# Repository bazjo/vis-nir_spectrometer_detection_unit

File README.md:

# vis-nir_spectrometer_detection_unit
This project contains a high-resolution detection unit for VIS/NIR spectroscopy using the Hamamatsu S1337-1010 photodiode and the Analog AD7768-1 24 Bit ADC.

It was developed as a student project in the summer term of 2020 in the course "Optical Spectroscopy and its Applications" at Cologne University of Applied Sciences.

## Getting Started

The PCB is designed to utilize an Arduino shield footprint for use with various breakout boards, such as ST Nucleo STM32 development boards or the avnet MiniZed development platform for Xilinx Zynq.

It features power filtering and an -5V inverter, the AD7768-1 DC to 204 kHz 24-Bit ADC (connected via SPI) with a 4.096 V ADR4540 and a photodiode front end featuring the AD8622 OpAmp. When a tunable clock is not available, i.e. when no FPGA is used, the main clock can be provided by an Si514 Any Frequency Programmable Oscillator (connected via I2C).

The photodiode is attached at the front to be mounted inside the spectrometer.

When assembling the PCB please look out for the bodges/errata. The PCB has been designed using kicad.

Demo applications are provided for the Arduino platform (just for the Si514 as the AD7768-1 requires 16-Bit SPI which is not yet supported by Arduino) and the STM32 platform. This application is designed for the Nucleo F401RE and was developed using the Crossley CrossWorks for ARM IDE. The code can be compiled with the trial version. This demo Application continuously sends data to a connected computer at 300 Sp/s via a serial connection.

## Theory of Operation

### Pinout
[jumpered] Pins must be connected by a designated jumper resistor.

Arduino Pin | STM32F401RE Pin | Connection
---|---|---
D0|PA3|none (!DRDY if not bodged)
D1|PA2|[jumpered] AD7768-1 !RESET
D2|PA10|[jumpered] AD7768-1 GPIO0
D3|PB3|[jumpered] AD7768-1 GPIO1
D4|PB5|[jumpered] AD7768-1 GPIO2
D5|PB4|[jumpered] AD7768-1 GPIO3
D6|PB10|[jumpered] AD7768-1 MCLK
D7|PA8|AD7768-1 !DRDY after bodge
D10|PB6|AD7768-1 !CS
D11|PA7|AD7768-1 MOSI
D12|PA6|AD7768-1 MISO
D13|PA5|AD7768-1 SCK
SDA|PB9|Si514 SDA
SCL|PB8|Si514 SCL

### Bodges/Errata
There are two problems with the pcb which are minor enough not to roll out a new revision
1. The Arduino RX/TX pins are used for GPIO. Unfortunately those Pins are used for the VCP connection on the Nucleo boards as well. The needed connection !DRDY is therefore rerouted to pin D7. This bodge can be performed by drilling the via on !DRDY with 0.8 mm drill bit and soldering a bodge wire between TP6 and D7.
2. When using the ADC on it's own, sync pulses can be generated via SPI. Those need to be send from SYNC_OUT to SYNC_IN. For this, bridge TP4 and TP5 with a 1206 0R resistor.

### PSU
The circuit uses three voltage rails. The 3V3 and 5V rails are used straight from the baseboard and are filtered through a 2-Stage LC PI-filter. The -5V rail is generated locally with TPS63700 inverter and subsequent LM2991 LDO. Power Planes are located on the second inner layer of the PCB. there are different planes for analog and digital ground, whose domains are joint below the high-speed adc interface to prevent loop currents.

### Oscillator
The Si514 Oscillator is attached via I2C and is equipped with pullup resistors. The source for the ADC MCLK can be selected between Si514 and baseboard via means of the resistor jumpers R24/R29. The tap R29 could also be used for MCLK monitoring.

### ADC + Frontend
The AD7768 was chosen for a few different reasons. First of all, it is a 24-Bit ADC suitable for low frequencies and even DC. Further, it features digital signal processing capabilities difficult to implement in a MCU. Most importantly, it allows for a wide range of decimation rates and a highly customizable sample rate so that acquisitions can be matched to the speed of a wavelength selective element. The ADC is connected via SPI. It is used in a pseudo-differential configuration with a 4.096 V reference ADR4540, to measure a voltage range between 0 an 4.096 V. The lowest possible sample rate with the highest decimation of 1024x is 300 Sp/s.

The ADC is paired with a transimpedance photodiode amplifier which is realized upon 1/2 of an AD8622 OpAmp. The values of the feedback network are matched in accordance to the photodiode sensitivity and speed. The photodiodes anode can be connected to ground via R23 or the diode can be reversed biased via R22. Reverse bias is generated through the other 1/2 of the AD8622 buffering an voltage divider R25/R26.

The photodiode is a Hamamatsu S1337-1010. It's spectral response from 190/340-1100 nm enables its use in VIS and certain NIR applications. The large area guarantees a high photosensitivity, and the rise time is fast enough for the desired spectroscopy application.

## Software Examples
The included software provides functions to interface with the hardware on the PCB.

The function `Set_Si514_Frequency()` configures the Si514 and has to be executed after every restart. It expects an array of register values which can be calculated through the Silab Utility provided in /resources/tools.

The functions to read an write from/to the AD7768-1 registers in general feature 8 bit wide addresses and values. An exemption is the result register, which is 24 bit wide an therefore is internally handled as an uint32.

After the ICs are configured, a SYNC pulse is triggered which starts the continuous adc capture. Every time a new sample is ready, a falling edge is presented to the MCU by the adc on !DRDY which is captured through an interrupt, and sets a flag, which enables a readout in the main program loop. Depending upon configuration of the variable `average_mode`, the result is either output through a serial connection right away, or after 256 samples have been averaged.

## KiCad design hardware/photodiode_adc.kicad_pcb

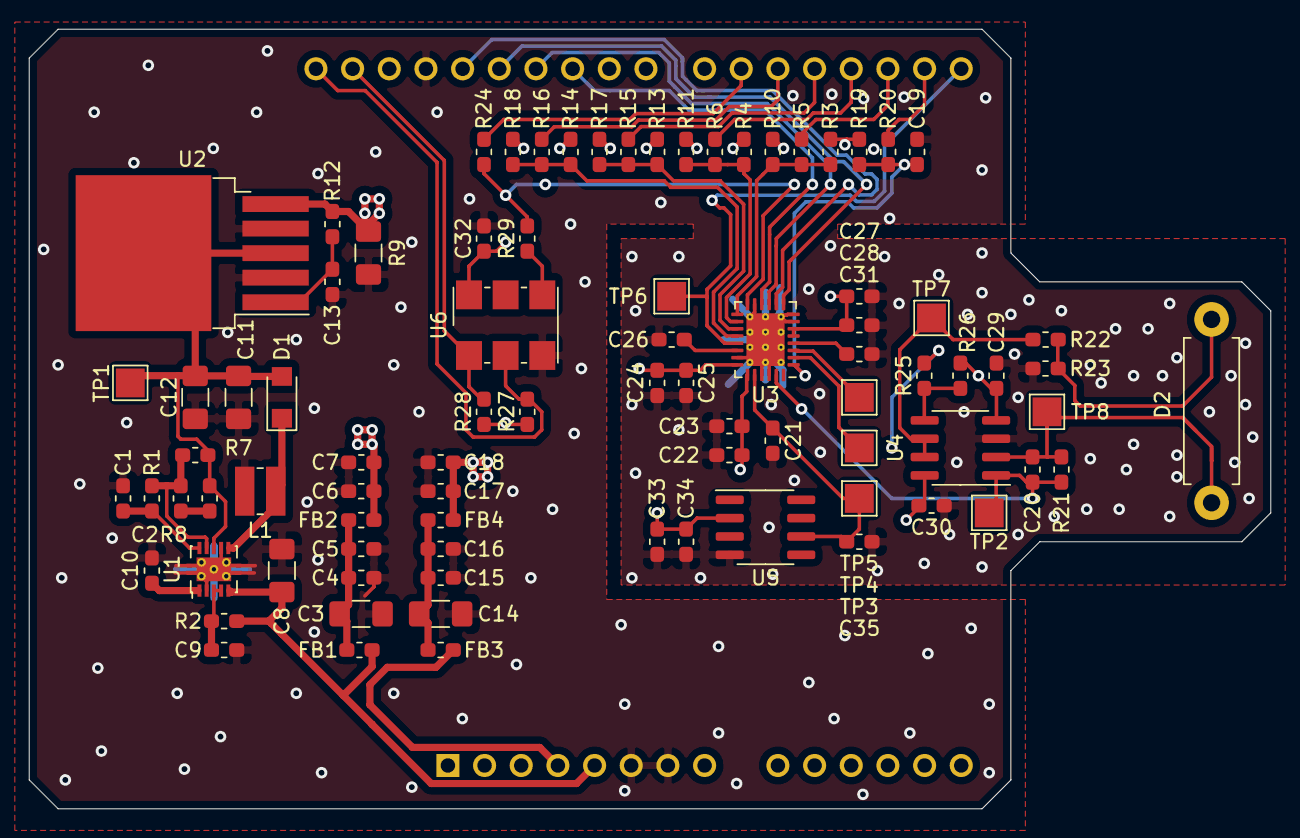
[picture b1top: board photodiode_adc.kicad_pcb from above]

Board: 4 copper layers, 86.0 x 54.0 mm, 86 parts (1 on the bottom side), 45 nets.

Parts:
A1: Arduino_UNO_R3; Arduino_UNO_R3_NoSilk
C1: 220n; C_0603_1608Metric_Pad1.05x0.95mm_HandSolder
C2: 10p; C_0603_1608Metric_Pad1.05x0.95mm_HandSolder
C3, C8, C12, C13, C14: 10u; C_1206_3216Metric_Pad1.42x1.75mm_HandSolder
C4, C6, C15, C17, C22, C24, C26, C27, C31, C33: 1u; C_0603_1608Metric_Pad1.05x0.95mm_HandSolder
C5, C7, C9, C16, C18, C19, C21, C23, C25, C28, C29, C30, C32, C34, C35: 100n; C_0603_1608Metric_Pad1.05x0.95mm_HandSolder
C10: 4n7; C_0603_1608Metric_Pad1.05x0.95mm_HandSolder
C11: 22u; C_1206_3216Metric_Pad1.42x1.75mm_HandSolder
C20: 360p; C_0603_1608Metric_Pad1.05x0.95mm_HandSolder
D1: D_Schottky; D_SMF
D2: D_Photo_ALT; R_Axial_DIN0411_L9.9mm_D3.6mm_P12.70mm_Horizontal
FB1, FB2, FB3, FB4: Ferrite_Bead_Small; C_0603_1608Metric_Pad1.05x0.95mm_HandSolder
L1: 4u7; L_Wuerth_MAPI-3020
R1: 150k; R_0603_1608Metric_Pad1.05x0.95mm_HandSolder
R2: 10R; R_0603_1608Metric_Pad1.05x0.95mm_HandSolder
R3, R4, R5, R6, R10, R11, R13, R14, R15, R16, R17, R18, R19, R20, R22, R23, R24, R29: 0R; R_0603_1608Metric_Pad1.05x0.95mm_HandSolder
R7: 742k; R_0603_1608Metric_Pad1.05x0.95mm_HandSolder
R8, R12: 100k; R_0603_1608Metric_Pad1.05x0.95mm_HandSolder
R9: 32k; R_0603_1608Metric_Pad1.05x0.95mm_HandSolder
R21: 42.2k; R_0603_1608Metric_Pad1.05x0.95mm_HandSolder
R25, R26: R; R_0603_1608Metric_Pad1.05x0.95mm_HandSolder
R27, R28: 4k7; R_0603_1608Metric_Pad1.05x0.95mm_HandSolder
TP1, TP2, TP3, TP4, TP5, TP6, TP7, TP8: TestPoint; TestPoint_Pad_2.0x2.0mm
U1: TPS63700; VSON-10-1EP_3x3mm_P0.5mm_EP1.65x2.4mm_ThermalVias
U2: LM2991; TO-263-5_TabPin6
U3: AD7768-1; QFN-28-1EP_4x5mm_P0.5mm_EP2.65x3.65mm_ThermalVias
U4: AD8622; SOIC-8_3.9x4.9mm_P1.27mm
U5: ADR452x; SOIC-8_3.9x4.9mm_P1.27mm
U6: Si514; Oscillator_SMD_IDT_JU6-6_7.0x5.0mm_P2.54mm

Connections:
+3V3: A1.4, C17.1, C18.1, C27.1, C28.1, C32.1, FB3.2, FB4.1, R3.1, R4.1, R13.1, R14.1, R19.1, R27.1, R28.1, U3.5, U3.6, U6.6
+5V: A1.5, C8.2, FB1.2, R2.2, U1.5
+5VA: C6.1, C7.1, C22.1, C23.1, C24.1, C25.1, C30.1, C33.1, C34.1, FB2.1, R25.2, U3.22, U3.23, U4.8, U5.2
-5VA: C13.2, C29.1, R12.1, R26.2, U2.5, U4.4
/0_ADC: R3.2, R5.2, R10.2, U3.15
/0_MCU: A1.17, R5.1
/1_ADC: R4.2, R6.2, R11.2, U3.16
/1_MCU: A1.18, R6.1
/2_ADC: R13.2, R15.2, R17.2, U3.17
/2_MCU: A1.19, R15.1
/3_ADC: R14.2, R16.2, R18.2, U3.18
/3_MCU: A1.20, R16.1
/MCLK: R24.2, R29.2, U3.14
/MISO: A1.27, U3.9
/MOSI: A1.26, U3.11
/RST_ADC: C19.2, R19.2, R20.2, U3.1
/RST_MCU: A1.16, R20.1
/SCK: A1.28, U3.10
/SCL: A1.32, R27.2, U6.2
/SDA: A1.31, R28.2, U6.1
/VREF: C21.1, C35.1, TP3.1, U3.24, U5.6
/V_REV: R22.2, TP7.1, U4.6, U4.7
/~CS~: A1.25, U3.12
/~DRDY~: A1.15, TP6.1, U3.19
GNDA: A1.6, A1.7, A1.29, C1.2, C3.2, C4.2, C5.2, C6.2, C7.2, C8.1, C9.1, C10.1, C11.1, C12.1, C13.1, C14.2, C15.2, C16.2, C17.2, C18.2, C19.1, C21.2, C22.2, C23.2, C24.2, C25.2, C26.2, C27.2, C28.2, C29.2, C30.2, C31.1, C32.2, C33.2, C34.2, C35.2, L1.2, R9.2, R10.1, R11.1, R17.1, R18.1, R23.2, U1.2, U1.7, U1.11, U2.2, U2.4, U3.7, U3.8, U3.13, U3.21, U3.25, U3.26, U3.29, U4.3, U5.4, U6.3
unnamed: A1.21, R24.1
unnamed: C1.1, R1.2, U1.10
unnamed: C2.1, R8.2
unnamed: C2.2, R1.1, R7.2, U1.9
unnamed: C3.1, C4.1, C5.1, FB1.1, FB2.2
unnamed: C9.2, R2.1, U1.3, U1.4
unnamed: C10.2, U1.1
unnamed: C11.2, C12.2, D1.2, R7.1, R8.1, TP1.1, U1.8, U2.3, U2.6
unnamed: C14.1, C15.1, C16.1, FB3.1, FB4.2
unnamed: C20.1, R21.1, TP2.1, U3.27, U4.1
unnamed: C20.2, D2.1, R21.2, TP8.1, U4.2
unnamed: C26.1, U3.20
unnamed: C31.2, U3.4
unnamed: D1.1, L1.1, U1.6
unnamed: D2.2, R22.1, R23.1
unnamed: R9.1, R12.2, U2.1
unnamed: R25.1, R26.1, U4.5
unnamed: R29.1, U6.4
unnamed: TP4.1, U3.2
unnamed: TP5.1, U3.3

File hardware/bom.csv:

Reference, Quantity, Value, Footprint, Datasheet
A1 ,1,"Arduino_UNO_R3","Module:Arduino_UNO_R3","https://www.arduino.cc/en/Main/arduinoBoardUno"
C1 ,1,"220n","Capacitor_SMD:C_0603_1608Metric_Pad1.05x0.95mm_HandSolder","~"
C10 ,1,"4n7","Capacitor_SMD:C_0603_1608Metric_Pad1.05x0.95mm_HandSolder","~"
C11 ,1,"22u","Capacitor_SMD:C_1206_3216Metric_Pad1.42x1.75mm_HandSolder","~"
C2 ,1,"10p","Capacitor_SMD:C_0603_1608Metric_Pad1.05x0.95mm_HandSolder","~"
C20 ,1,"360p","Capacitor_SMD:C_0603_1608Metric_Pad1.05x0.95mm_HandSolder","~"
C21 C19 C5 C7 C16 C18 C9 C32 C34 C35 C23 C25 C28 C29 C30 ,15,"100n","Capacitor_SMD:C_0603_1608Metric_Pad1.05x0.95mm_HandSolder","~"
C3 C14 C8 C12 C13 ,5,"10u","Capacitor_SMD:C_1206_3216Metric_Pad1.42x1.75mm_HandSolder","~"
C4 C6 C15 C17 C33 C26 C31 C22 C24 C27 ,10,"1u","Capacitor_SMD:C_0603_1608Metric_Pad1.05x0.95mm_HandSolder","~"
D1 ,1,"D_Schottky","Diode_SMD:D_SMF","~"
D2 ,1,"D_Photo_ALT","Resistor_THT:R_Axial_Power_L48.0mm_W12.5mm_P7.62mm_Vertical","~"
FB1 FB2 FB3 FB4 ,4,"Ferrite_Bead_Small","Capacitor_SMD:C_0603_1608Metric_Pad1.05x0.95mm_HandSolder","~"
L1 ,1,"4u7","Inductor_SMD:L_Wuerth_MAPI-3020","~"
R1 ,1,"150k","Resistor_SMD:R_0603_1608Metric_Pad1.05x0.95mm_HandSolder","~"
R2 ,1,"10R","Resistor_SMD:R_0603_1608Metric_Pad1.05x0.95mm_HandSolder","~"
R21 ,1,"42.2k","Resistor_SMD:R_0603_1608Metric_Pad1.05x0.95mm_HandSolder","~"
R25 R26 ,2,"R","Resistor_SMD:R_0603_1608Metric_Pad1.05x0.95mm_HandSolder","~"
R28 R27 ,2,"4k7","Resistor_SMD:R_0603_1608Metric_Pad1.05x0.95mm_HandSolder","~"
R4 R6 R11 R14 R16 R18 R13 R15 R17 R3 R5 R10 R19 R20 R24 R22 R23 R29 ,18,"0R","Resistor_SMD:R_0603_1608Metric_Pad1.05x0.95mm_HandSolder","~"
R7 ,1,"742k","Resistor_SMD:R_0603_1608Metric_Pad1.05x0.95mm_HandSolder","~"
R8 R12 ,2,"100k","Resistor_SMD:R_0603_1608Metric_Pad1.05x0.95mm_HandSolder","~"
R9 ,1,"32k","Resistor_SMD:R_0603_1608Metric_Pad1.05x0.95mm_HandSolder","~"
TP4 TP5 TP6 TP2 TP3 TP7 TP1 TP8 ,8,"TestPoint","TestPoint:TestPoint_Pad_2.0x2.0mm","~"
U1 ,1,"TPS63700","Package_SON:VSON-10-1EP_3x3mm_P0.5mm_EP1.65x2.4mm_ThermalVias",""
U2 ,1,"LM2991","Package_TO_SOT_SMD:TO-263-5_TabPin6",""
U3 ,1,"AD7768-1","Package_DFN_QFN:QFN-28-1EP_4x5mm_P0.5mm_EP2.65x3.65mm_ThermalVias",""
U4 ,1,"AD8622","Package_SO:SOIC-8_3.9x4.9mm_P1.27mm",""
U5 ,1,"ADR452x","Package_SO:SOIC-8_3.9x4.9mm_P1.27mm",""
U6 ,1,"Si514","Oscillator:Oscillator_SMD_IDT_JU6-6_7.0x5.0mm_P2.54mm",""

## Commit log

2020-07-28 add kicad project files for rev 0.1
2020-07-28 add datasheets
2020-07-28 add cubemx configuration
2020-07-28 refactor cubemx configuration and add crossworks project
2020-07-28 add register calc utility for si514, add arduino demo for si514
2020-07-28 refactor documentation
2020-09-22 implement i2c and spi prototype for stm32
2020-09-23 add functions for writing/reading regular AD7768-1 registers
2020-09-24 add adc continous readout example
2020-10-08 cleanup stm code
2020-10-08 remove arduino prototype
2020-10-08 update documatation
2020-10-08 fix typo
